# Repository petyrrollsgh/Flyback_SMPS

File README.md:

# Flyback_SMPS
+12V, -12V, 5V, 3.3V DC power supply with 24V DC input with flyback topology

# Split-Rail, Switch-Mode, Power Supply
  For the Universal Sensor Interface (USI) project, I needed a power supply capable of powering op-amps with both +12V and -12V rails as well as +5V and might as well have +3.3V too.  I had previously designed (KiCad), had fabricated (from JPLPCB), ordered components (Mouser), hand-assembled and tested a very small board.  But the purpose of that board was mostly to figure out the entire workflow and practice soldering.  This was my first attempt to actually build something useful.  It worked, but there were a couple of minor errors that I was able to fix without ordering new boards.  However, the schematic shown below is corrected from the actual tested board.  I am confident the new schematic will work as intended.  Most of the errors were minor such as inverted diodes and incorrect values for the voltage adjustment.  The major critical addition was that of R22 a 10K resistor.  It turns out that without some current draw the fly back circuit will quickly overheat the protection circuit composed of  diodes D4 and D5.  

  The circuit was based largely on the LM2586 data sheet and followed the “Figure 32. Triple-Output Flyback Regulator” schematic.  The data sheet gives recommendations for coils to use and I chose the Q4338-BL coil.  The outputs were then sent to LT1963 and LT3015 LDO voltage regulators with the +5V output used to drive the regulated +3.3V output.

  Out of an abundance of caution I used a 4-layer board to ensure all power circuits had clear ground paths for current flow.  The extra cost of a 4-layer board is minor in comparison to the component cost and my own labor.  I was also careful to isolate the switch mode part of the system from the LDO parts of the circuit.  

  I spent a considerable amount of time studying how to ensure correct current flow paths to reduce noise.  There are many lectures and videos on the subject which emphasize that energy flow passes through the space between wires and/or circuit paths and not is the circular path that most schematics tend to emphasize.  But putting this concept into action became a difficult practical problem.  I just didn’t know if my routing was idiotic or not.  Eventually I decided that the best circuit design principle was to clearly determine where current traveled between components and ensure that all tracks out of a device were matched with a suitable ground plane through which the return current could pass and that no other subcircuits used or crossed that pathway.  My best analogy to the entire concept was that of an AC signal connected to a twisted pair of wires which then separated and terminated in a “T” to form an antenna.  The best circuit design was to keep the wires as tightly twisted as possible by providing a large and unique ground return path.  Inevitably at actual circuit devices these paths must separate forming an antenna.  I tried to keep these separations as minimal as possible.  

  All components were hand soldered and this was time consuming and difficult work.  For future circuits, I used the silk screen and a modified a toaster oven with a programmable power control to ramp up the temperature to appropriate levels.  The stainless-steel screen was less than 10 bucks, a minimal cost compared to my time, and produced superior solders.  This even made soldering 603 capacitors a breeze.  However, the screen tended to put down too much paste for the finer 0.5 mm spacing of VSSOP devices but was great for the larger spacing on SOIC devices.  
LM2586 4-V to 40-V, 3-A Step-Up Wide VIN Flyback Regulator datasheet (Rev. E)

  The KiCad files are on GitHub at https://github.com/petyrrollsgh/Flyback_SMPS.  Use these as a good starting point for your own design.  Double check everything. Many footprints will be missing.   If you don’t use KiCad then I suggest you download a copy and use that to translate the schematic to whatever you are using.  Better yet just redraw the schematic in you ECAD software and create your own PCB layout using my project as helpful suggestions.

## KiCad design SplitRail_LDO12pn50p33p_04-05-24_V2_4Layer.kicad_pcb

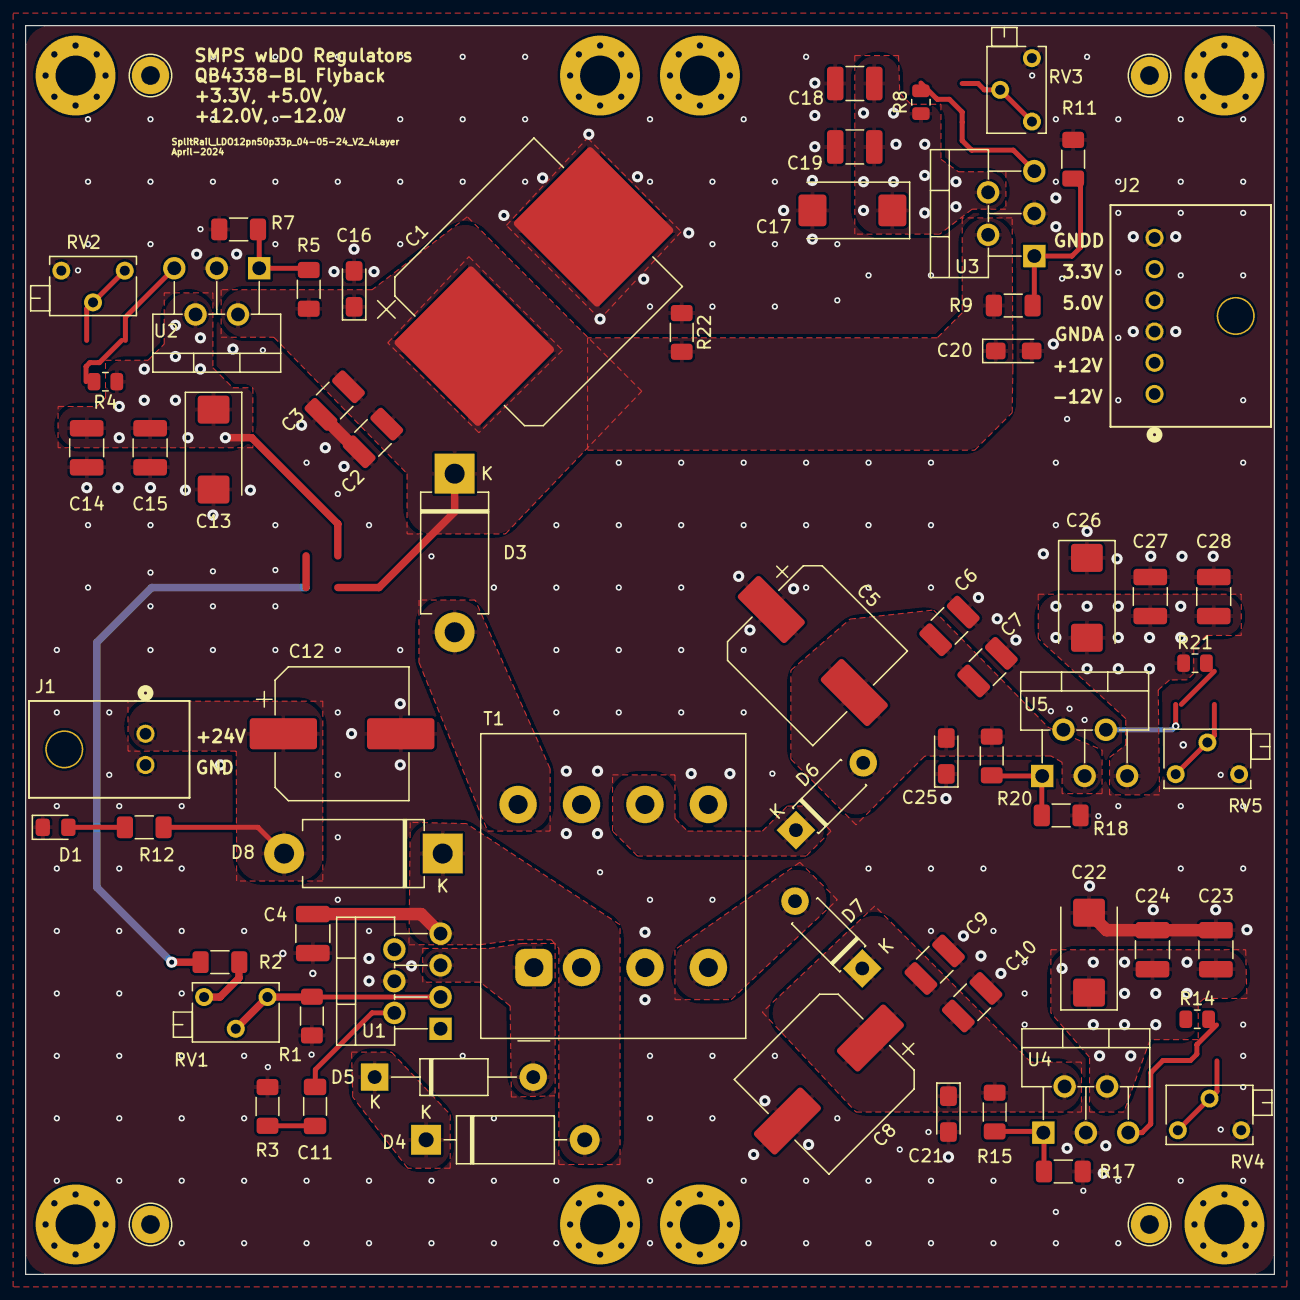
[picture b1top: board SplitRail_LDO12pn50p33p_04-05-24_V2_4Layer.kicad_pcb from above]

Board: 4 copper layers, 100.0 x 100.0 mm, 77 parts (0 on the bottom side), 28 nets.

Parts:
C1: 1500uf; CP_Elec_16x22_HandSolder
C2, C6, C9: 22uf; C_1210_3225Metric_Pad1.33x2.70mm_HandSolder
C3, C7, C10, C14, C18, C23, C27: 10uf; C_1210_3225Metric_Pad1.33x2.70mm_HandSolder
C4, C15, C19, C24, C28: 1uf; C_1210_3225Metric_Pad1.33x2.70mm_HandSolder
C5, C8, C12: 120uf; CP_Elec_10x14.3_HandSolder
C11: .33uf; C_1206_3216Metric_Pad1.33x1.80mm_HandSolder
C13, C17, C22, C26: 47uf; CP_EIA-7343-43_Kemet-X_Pad2.25x2.55mm_HandSolder
C16, C20, C21, C25: 1uf; CP_EIA-3216-18_Kemet-A_Pad1.58x1.35mm_HandSolder
D1: LED; LED_0805_2012Metric_Pad1.15x1.40mm_HandSolder
D3, D8: 1N5822; D_DO-201AD_P12.70mm_Horizontal
D4: S18A; D_DO-15_P12.70mm_Horizontal
D5: MUR120; D_DO-41_SOD81_P12.70mm_Horizontal
D6, D7: D_SB160; D_DO-41_SOD81_P7.62mm_Horizontal
H1, H2, H3, H4, H5, H6, H7, H8: MountingHole; MountingHole_3.2mm_M3_Pad_Via
J1: TE_EP25_2; Conn_EP25_1744426-2
J2: TE_EP25-6; Conn_EP25_1744426-6
R1, R3, R12: 2k; R_1206_3216Metric_Pad1.30x1.75mm_HandSolder
R2: 6.04k; R_1206_3216Metric_Pad1.30x1.75mm_HandSolder
R4: 1.5k; R_0805_2012Metric
R5: 4.99k; R_1206_3216Metric_Pad1.30x1.75mm_HandSolder
R7, R11, R17, R18: 1k; R_1206_3216Metric_Pad1.30x1.75mm_HandSolder
R8: 866; R_0805_2012Metric
R9: 3300; R_1206_3216Metric_Pad1.30x1.75mm_HandSolder
R14, R21: 4.42k; R_0805_2012Metric
R15: 13.3k; R_1206_3216Metric_Pad1.30x1.75mm_HandSolder
R20: 9.1k; R_1206_3216Metric_Pad1.30x1.75mm_HandSolder
R22: 10k; R_1206_3216Metric_Pad1.30x1.75mm_HandSolder
RV1: 0-5k; Potentiometer_Bourns_3266X_Horizontal
RV2, RV3, RV4, RV5: 0-1k; Potentiometer_Bourns_3266X_Horizontal
T1: Q4338-BL
TPG1, TPG2, TPG3, TPG4: 5001; TestPoint_Loop_D2.54mm_Drill1.5mm_Beaded
U1: LM2586T-adj; TO-220-7_P2.54x3.7mm_StaggerOdd_Lead3.8mm_Vertical
U2, U3, U4: LT1963-adj; TO-220-5_P3.4x3.7mm_StaggerOdd_Lead3.8mm_Vertical
U5: LT3015-adj; TO-220-5_P3.4x3.7mm_StaggerOdd_Lead3.8mm_Vertical

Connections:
+3.3V: C17.1, C18.1, C19.1, J2.5, R8.1, U3.4 (OUT)
+5.0V: C13.1, C14.1, C15.1, J2.4, R4.1, U2.4 (OUT)
+5_UR: C1.1, C2.2, C3.2, C16.1, C20.1, D3.1 (K), R2.2, R5.1, R9.1, R22.2, U2.2 (IN), U3.2 (IN)
+12_UR: C8.1, C9.2, C10.2, C21.1, D7.1 (K), R15.1, U4.2 (IN)
+24Vin: C4.2, D4.2 (A2), D8.1 (K), T1.2 (IN+), U1.7 (VIN)
+V: C12.1, D8.2 (A), J1.1, R12.1
+V1Reg: C22.1, C23.1, C24.1, J2.2, R14.2, U4.4 (OUT)
-12_UR: C5.2, C6.1, C7.1, C25.2, D6.2 (A), R20.1, U5.3 (IN)
-V1Reg: C26.2, C27.2, C28.2, J2.1, R21.1, U5.5 (OUT)
/+5T: D3.2 (A), T1.8 (OUT1B)
/+12T: D7.2 (A), T1.4 (OUT2B)
/-12T: D6.1 (K), T1.6 (OUT2A)
/COMP: C11.2, U1.2 (COMP)
/FB: R1.2, RV1.1, RV1.2, U1.3 (FEEDBACK)
/SW: D5.2 (A), T1.1 (IN-), U1.5 (SWITCH)
/d: D4.1 (A1), D5.1 (K)
/e: R4.2, RV2.1, RV2.2, U2.5 (ADJ)
/g: R8.2, RV3.1, RV3.2, U3.5 (ADJ)
/i: R14.1, RV4.1, RV4.2, U4.5 (ADJ)
/k: R21.2, RV5.1, RV5.2, U5.4 (ADJ)
/shdn12n: R18.1, R20.2, U5.1 (~SHDN)
/shdn12p: R15.2, R17.1, U4.1 (~SHDN)
/shdn33p: R9.2, R11.1, U3.1 (~SHDN)
/shdn50p: R5.2, R7.1, U2.1 (~SHDN)
Earth: C1.2, C2.1, C3.1, C4.1, C5.1, C6.2, C7.2, C8.2, C9.1, C10.1, C12.2, C13.2, C14.2, C15.2, C16.2, C17.2, C18.2, C19.2, C20.2, C21.2, C22.2, C23.2, C24.2, C25.1, C26.1, C27.1, C28.1, D1.1 (K), J1.2, J2.3, J2.6, R1.1, R3.1, R7.2, R11.2, R17.2, R18.2, R22.1, RV2.3, RV3.3, RV4.3, RV5.3, T1.3 (OUT2A), T1.5 (OUT2B), T1.7 (OUT1A), TPG1.1, TPG2.1, TPG3.1, TPG4.1, U1.4 (GND), U2.3 (GND), U3.3 (GND), U4.3 (GND), U5.2 (GND)
unnamed: C11.1, R3.2
unnamed: D1.2 (A), R12.2
unnamed: R2.1, RV1.3
